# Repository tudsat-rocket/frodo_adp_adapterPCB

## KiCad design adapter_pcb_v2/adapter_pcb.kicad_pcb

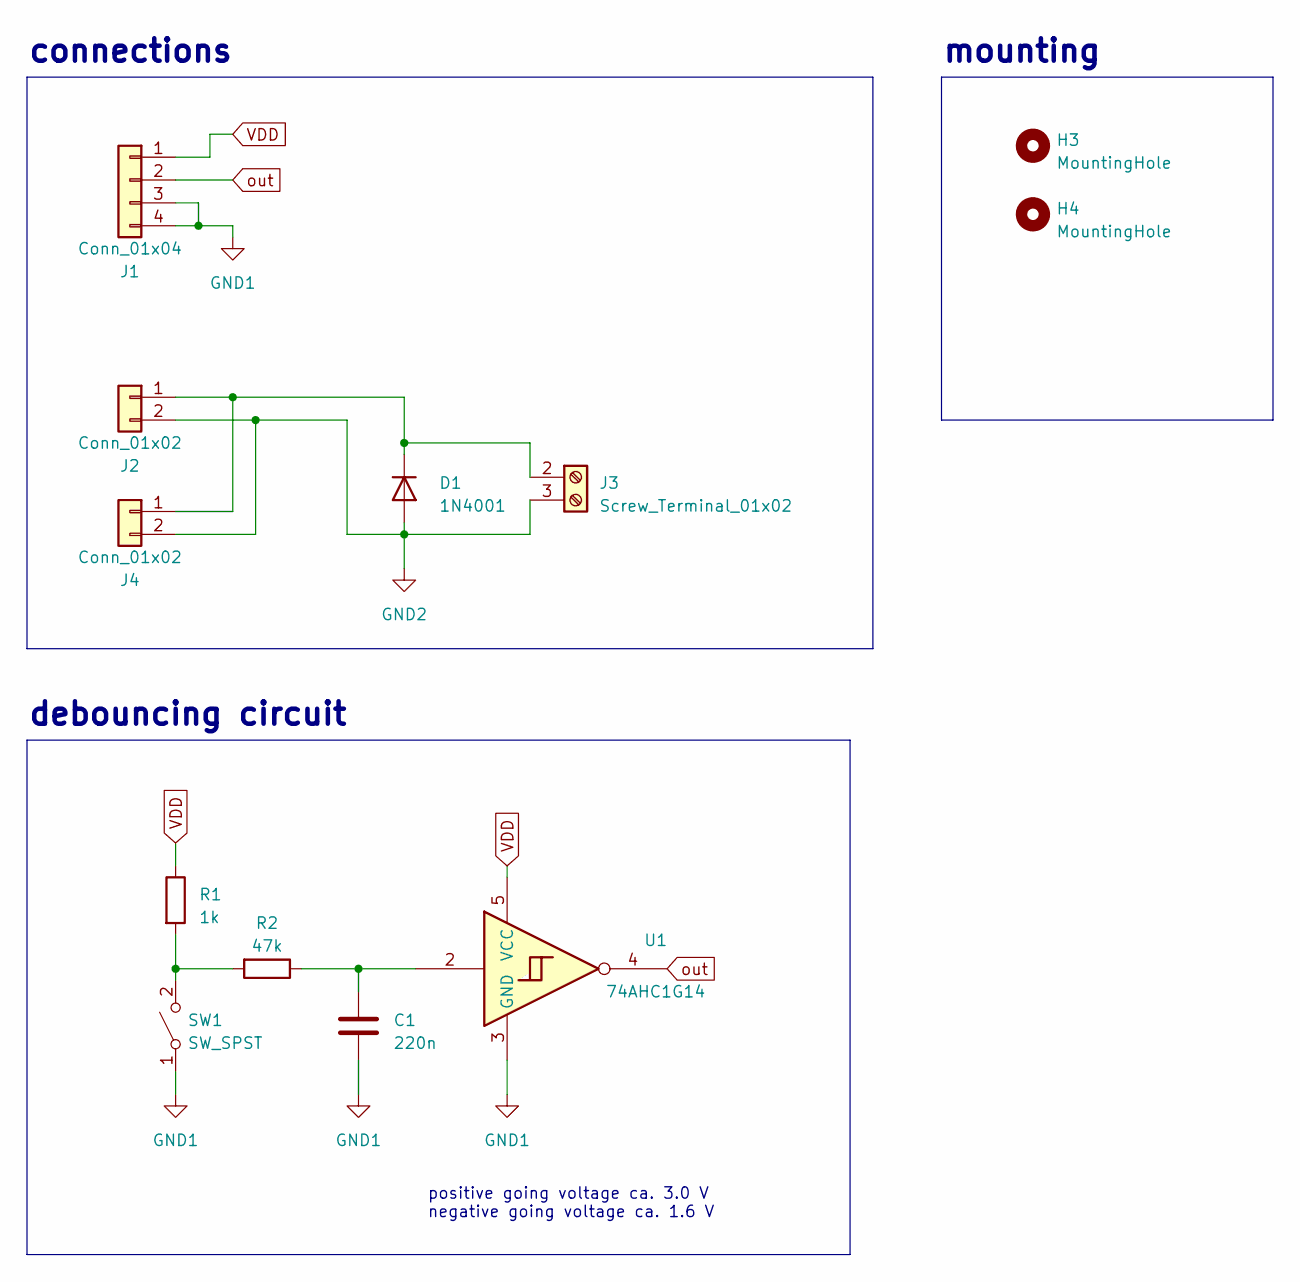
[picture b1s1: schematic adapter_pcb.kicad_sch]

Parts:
C1: 220n; C_0603_1608Metric_Pad1.08x0.95mm_HandSolder
D1: 1N4001; D_SOD-128
H3, H4: MountingHole; MountingHole_3.2mm_M3
J1: Conn_01x04; JST_GH_SM04B-GHS-TB_1x04-1MP_P1.25mm_Horizontal
J2, J4: Conn_01x02; Molex_Micro-Fit_3.0_43650-0210_1x02-1MP_P3.00mm_Horizontal
J3: Screw_Terminal_01x02; FLTS22WR00
R1: 1k; R_0603_1608Metric_Pad0.98x0.95mm_HandSolder
R2: 47k; R_0603_1608Metric_Pad0.98x0.95mm_HandSolder
SW1: SW_SPST; 430133050816
U1: 74AHC1G14; SOT-353_SC-70-5

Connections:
GND1: C1.2, J1.3, J1.4, SW1.1 (A), U1.3 (GND)
GND2: D1.2 (A), J2.2, J3.3, J4.2
unnamed: C1.1, R2.1, U1.2
unnamed: D1.1 (K), J2.1, J3.2, J4.1
unnamed: R1.2, R2.2, SW1.2 (B)
VDD: J1.1, R1.1, U1.5 (VCC)
out: J1.2, U1.4

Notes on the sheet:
mounting
debouncing circuit
connections
positive going voltage ca. 3.0 V negative going voltage ca. 1.6 V

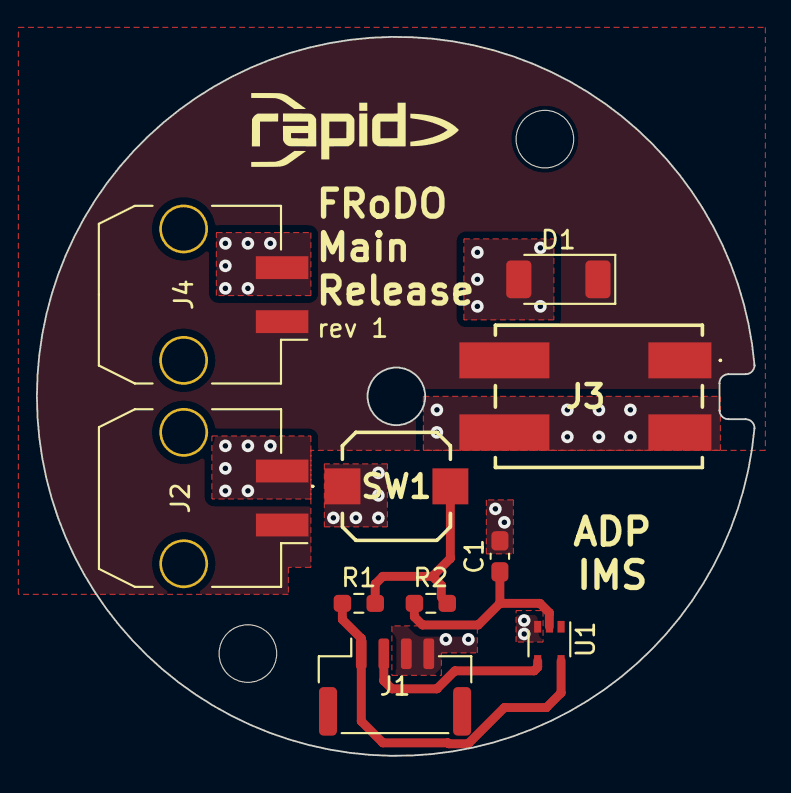
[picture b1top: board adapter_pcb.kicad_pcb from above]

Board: 2 copper layers, 39.9 x 39.9 mm, 12 parts (0 on the bottom side), 7 nets.

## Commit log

2024-02-01 Add silkscreen for ordering
